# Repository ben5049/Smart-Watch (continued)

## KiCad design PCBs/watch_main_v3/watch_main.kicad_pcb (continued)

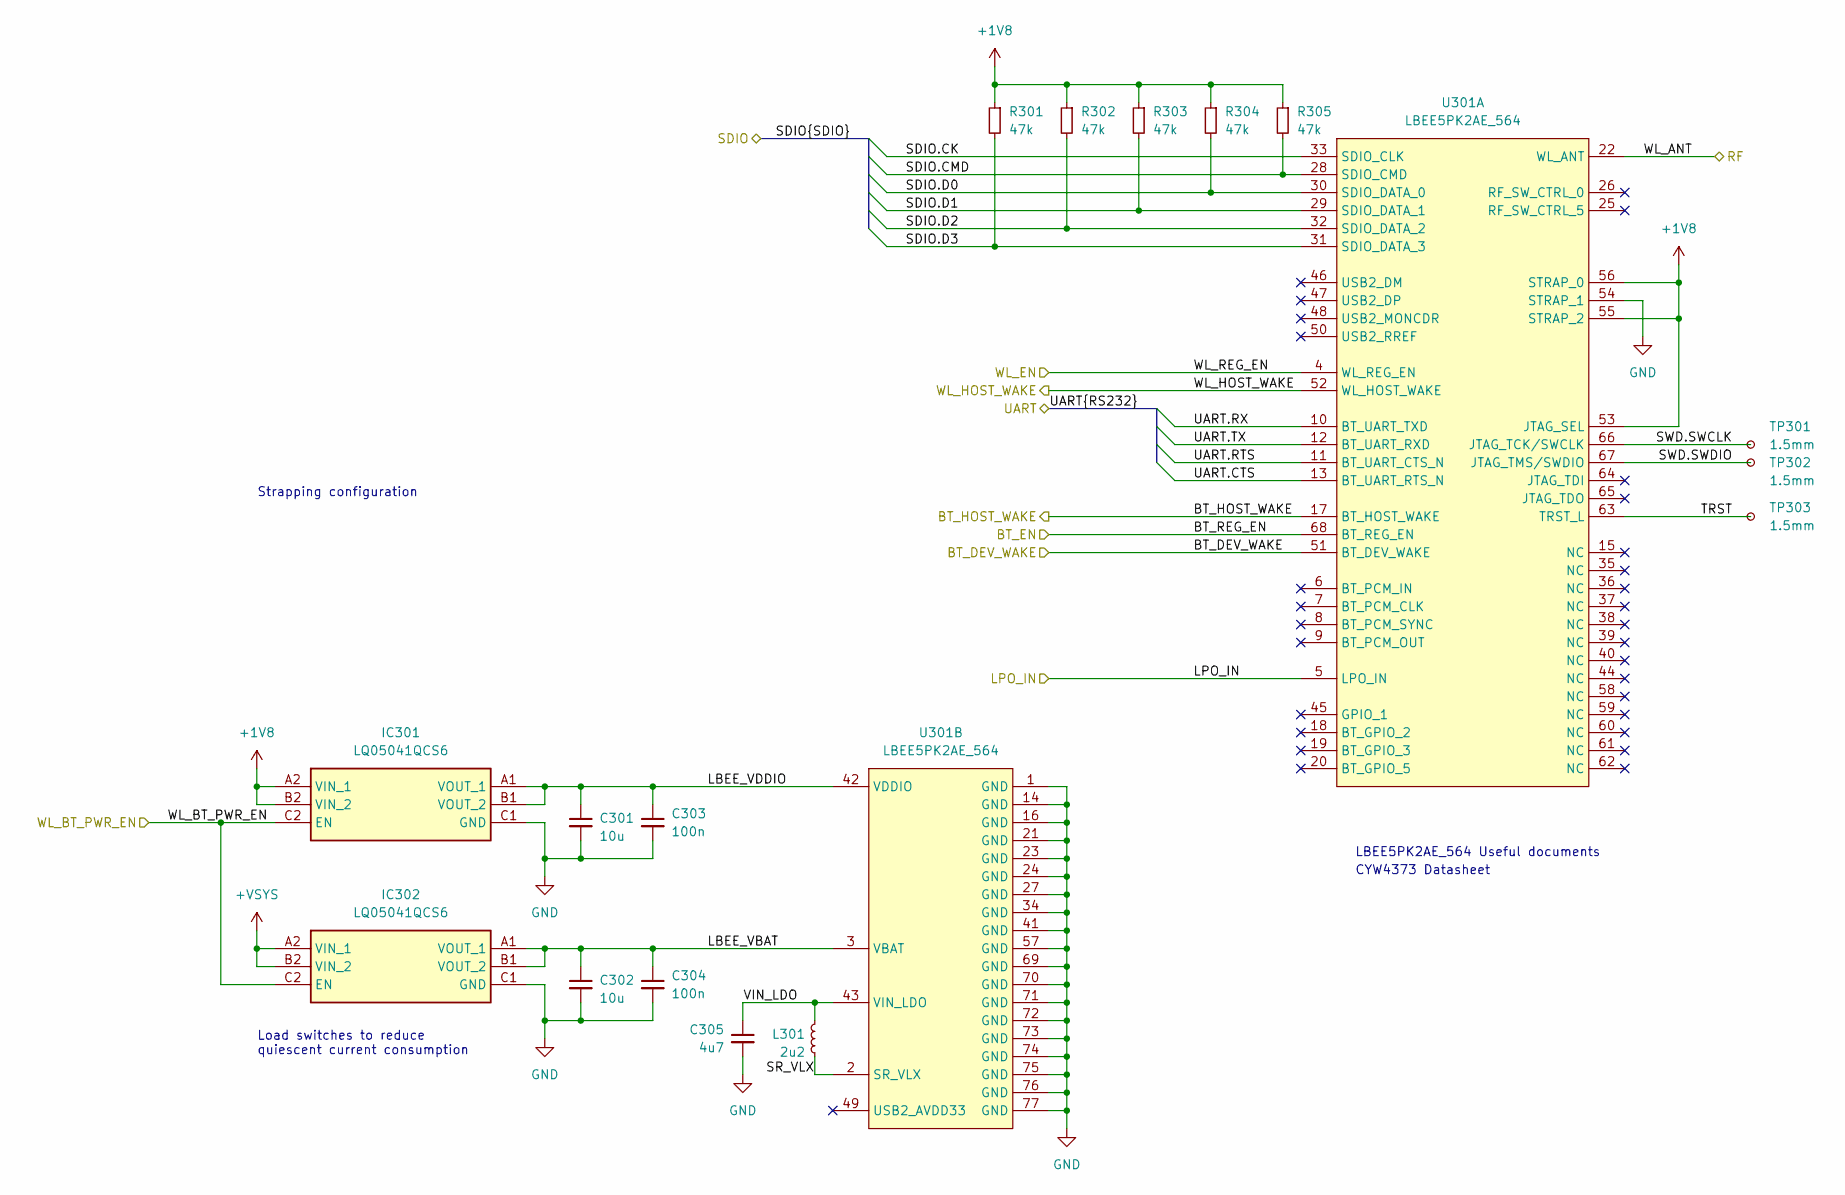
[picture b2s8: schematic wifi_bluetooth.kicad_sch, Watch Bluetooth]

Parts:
C301, C302: 10u; C_0402_1005Metric
C303, C304: 100n; C_0402_1005Metric
C305: 4u7; C_0402_1005Metric
IC301, IC302: LQ05041QCS6; BGA6C50P2X3_97X147X60; Manufacturer_Part_Number LQ05041QCS6
L301: 2u2; L_Murata_DFE201610P
R301, R302, R303, R304, R305: 47k; R_0402_1005Metric
TP301, TP302, TP303: 1.5mm; TestPoint_Pad_D1.5mm
U301: LBEE5PK2AE_564; LBEE5PK2AE-564

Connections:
+1V8: IC301.A2 (VIN_1), IC301.B2 (VIN_2), R301.1, R302.1, R303.1, R304.1, R305.1, U301.53 (JTAG_SEL), U301.55 (STRAP_2), U301.56 (STRAP_0); also elsewhere on the board
+VSYS: IC302.A2 (VIN_1), IC302.B2 (VIN_2); also elsewhere on the board
/BT_DEV_WAKE: U301.51 (BT_DEV_WAKE); also elsewhere on the board
/BT_EN: U301.68 (BT_REG_EN); also elsewhere on the board
/BT_HOST_WAKE: U301.17 (BT_HOST_WAKE); also elsewhere on the board
/RF_2.4G/5G: U301.22 (WL_ANT); also elsewhere on the board
/SDMMC2.CK: U301.33 (SDIO_CLK); also elsewhere on the board
/SDMMC2.CMD: R305.2, U301.28 (SDIO_CMD); also elsewhere on the board
/SDMMC2.D0: R304.2, U301.30 (SDIO_DATA_0); also elsewhere on the board
/SDMMC2.D1: R303.2, U301.29 (SDIO_DATA_1); also elsewhere on the board
/SDMMC2.D2: R302.2, U301.32 (SDIO_DATA_2); also elsewhere on the board
/SDMMC2.D3: R301.2, U301.31 (SDIO_DATA_3); also elsewhere on the board
/USART2.CTS: U301.13 (BT_UART_RTS_N); also elsewhere on the board
/USART2.RTS: U301.11 (BT_UART_CTS_N); also elsewhere on the board
/USART2.RX: U301.10 (BT_UART_TXD); also elsewhere on the board
/USART2.TX: U301.12 (BT_UART_RXD); also elsewhere on the board
/WL_BT_PWR_EN: IC301.C2 (EN), IC302.C2 (EN); also elsewhere on the board
/WL_EN: U301.4 (WL_REG_EN); also elsewhere on the board
/WL_HOST_WAKE: U301.52 (WL_HOST_WAKE); also elsewhere on the board
/WL_LPO_IN: U301.5 (LPO_IN); also elsewhere on the board
/WiFi and Bluetooth/LBEE_VBAT: C302.1, C304.1, IC302.A1 (VOUT_1), IC302.B1 (VOUT_2), U301.3 (VBAT)
/WiFi and Bluetooth/LBEE_VDDIO: C301.1, C303.1, IC301.A1 (VOUT_1), IC301.B1 (VOUT_2), U301.42 (VDDIO)
/WiFi and Bluetooth/SR_VLX: L301.2, U301.2 (SR_VLX)
/WiFi and Bluetooth/SWD.SWCLK: TP301.1, U301.66 (JTAG_TCK/SWCLK)
/WiFi and Bluetooth/SWD.SWDIO: TP302.1, U301.67 (JTAG_TMS/SWDIO)
/WiFi and Bluetooth/TRST: TP303.1, U301.63 (TRST_L)
/WiFi and Bluetooth/VIN_LDO: C305.1, L301.1, U301.43 (VIN_LDO)
GND: C301.2, C302.2, C303.2, C304.2, C305.2, IC301.C1 (GND), IC302.C1 (GND), U301.1 (GND), U301.14 (GND), U301.16 (GND), U301.21 (GND), U301.23 (GND), U301.24 (GND), U301.27 (GND), U301.34 (GND), U301.41 (GND), U301.54 (STRAP_1), U301.57 (GND), U301.69 (GND), U301.70 (GND), U301.71 (GND), U301.72 (GND), U301.73 (GND), U301.74 (GND), U301.75 (GND), U301.76 (GND), U301.77 (GND); also elsewhere on the board

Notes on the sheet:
Strapping configuration
LBEE5PK2AE_564 Useful documents
Load switches to reduce quiescent current consumption
CYW4373 Datasheet

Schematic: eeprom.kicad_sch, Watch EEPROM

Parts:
IC1801: M24256X-FCU6T_VF; BGA4C50P2X2_70X98X33; Mouser Part Number 511-M24256X-FCU6T/VF

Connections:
+1V8: IC1801.A1 (VCC); also elsewhere on the board
/I2C1.SCL: IC1801.A2 (SCL); also elsewhere on the board
/I2C1.SDA: IC1801.B1 (SDA); also elsewhere on the board
GND: IC1801.B2 (VSS); also elsewhere on the board

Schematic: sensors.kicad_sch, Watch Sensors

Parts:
C1301: 220n; C_0402_1005Metric
C1302, C1304, C1305, C1306, C1307: 100n; C_0402_1005Metric
C1303: 10u; C_0402_1005Metric
IC1301: IIS2MDCTR; Mouser Part Number 511-IIS2MDCTR
IC1302: OPT3004DNPR; SON65P200X200X65-7N-D; Mouser Part Number 595-OPT3004DNPR
U1301: LSM6DSO16IS; LGA14_LSM6_STM

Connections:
+1V8: C1302.1, C1303.1, C1304.1, C1305.1, C1306.1, C1307.1, IC1301.9 (VDD), IC1301.10 (VDD_IO), IC1302.1 (VDD), U1301.2 (MSDA), U1301.3 (MSCL), U1301.5 (VDD_IO), U1301.8 (VDD); also elsewhere on the board
/ALS_INT: IC1302.5 (INT); also elsewhere on the board
/I2C3.SCL: IC1301.1 (SCL/SPC), IC1302.4 (SCL); also elsewhere on the board
/I2C3.SDA: IC1301.4 (SDA/SDI/SDO), IC1302.6 (SDA); also elsewhere on the board
/IMU_INT1: U1301.4 (INT1); also elsewhere on the board
/IMU_INT2: U1301.9 (INT2); also elsewhere on the board
/MAG_INT: IC1301.7 (INT/DRDY); also elsewhere on the board
/SPI1.CS: U1301.12 (CS); also elsewhere on the board
/SPI1.MISO: U1301.1 (SDO/SA0); also elsewhere on the board
/SPI1.MOSI: U1301.14 (SDA); also elsewhere on the board
/SPI1.SCK: U1301.13 (SCL); also elsewhere on the board
/Sensors/C1: C1301.1, IC1301.5 (C1)
GND: C1301.2, C1302.2, C1303.2, C1304.2, C1305.2, C1306.2, C1307.2, IC1301.6 (GND_1), IC1301.8 (GND_2), IC1302.2 (ADDR), IC1302.3 (GND), IC1302.7 (EP), U1301.6 (GND), U1301.7 (GND); also elsewhere on the board

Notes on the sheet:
Address = 0x1E
Address = 0x6A (SA0=0)
Address = 0x44 (ADDR=0)
Typical application: LSM6DSO16IS datasheet p25
Typical application: IIS2MDCTR datasheet p19
Typical application: OPT3004 datasheet p19

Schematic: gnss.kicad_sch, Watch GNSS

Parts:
C401: 10n; C_0402_1005Metric
C402: 120p; C_0402_1005Metric
C403: 100n; C_0402_1005Metric
FL401: B39162B4327P810; mouser part number 871-B39162B4327P810; digikey description FILTER SAW 5SMD
IC401: BGA725L6E6327FTSA1; BGS12SN6E6327XTSA1; Mouser Part Number 726-BGA725L6E6327FTS
L401: 7n5; L_0402_1005Metric
R401: 10k; R_0402_1005Metric
U401: TESEO-LIV3FL; TESEOLIV3FL; Mouser Part Number 511-TESEO-LIV4FTR

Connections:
+1V8: C403.1, U401.6 (VBAT), U401.7 (VCCIO), U401.8 (VCC); also elsewhere on the board
/GNSS/ANT_OFF: IC401.6 (PON), R401.1, U401.13 (ANT_OFF)
/GNSS/LNA_IN: IC401.5 (AI), L401.2
/GNSS/LNA_OUT: FL401.1 (IN), IC401.3 (AO)
/GNSS/RF_IN: C402.2, U401.11 (RF_IN)
/GNSS/SAW_OUT: C402.1, FL401.4 (OUT)
/GNSS/VCC_RF: C401.1, IC401.2 (VCC), U401.14 (VCC_RF)
/GNSS_PPS: U401.4 (PPS); also elsewhere on the board
/GNSS_RST: U401.9 (NRESET); also elsewhere on the board
/GNSS_WAKEUP: U401.5 (WAKEUP); also elsewhere on the board
/RF_1.575G: L401.1; also elsewhere on the board
/USART1.RX: U401.2 (UART-TX); also elsewhere on the board
/USART1.TX: U401.3 (UART-RX); also elsewhere on the board
GND: C401.2, C403.2, FL401.2 (GND_1), FL401.3 (GND_2), FL401.5 (GND_3), IC401.1 (GND), IC401.4 (GNDRF), R401.2, U401.1 (GND), U401.10 (GND_RF_1), U401.12 (GND_RF_2); also elsewhere on the board

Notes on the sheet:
UM2980 p12

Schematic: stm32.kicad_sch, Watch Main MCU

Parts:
C801, C802, C803, C804: 6p; C_0402_1005Metric
R801, R802, R803, R804, R805, R806, R807, R808, R809, R810, R811, R812: 4k7; R_0402_1005Metric
TP801, TP802, TP803, TP804: 1.5mm; TestPoint_Pad_D1.5mm
U801: STM32U5G9ZJJ6Q; UFBGA144_STM
Y801: 16MHz; Crystal_SMD_2016-4Pin_2.0x1.6mm
Y802: 32.768kHz; Crystal_SMD_2012-2Pin_2.0x1.2mm

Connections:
+1V8: R801.1, R802.1, R803.1, R804.1, R805.1, R806.1, R807.1, R808.1, R810.1, R812.1; also elsewhere on the board
+3V3: R809.1, R811.1; also elsewhere on the board
/ADF1_CCK0: U801.K6 (PE9); also elsewhere on the board
/ADF1_SDI0: U801.J7 (PE10); also elsewhere on the board
/ALS_INT: U801.J6 (PG1); also elsewhere on the board
/AVDDEN: U801.D3 (PE6); also elsewhere on the board
/AVDD_ADC: U801.M2 (PA3); also elsewhere on the board
/BTN: U801.M9 (PB15); also elsewhere on the board
/BT_DEV_WAKE: U801.E11 (PI2); also elsewhere on the board
/BT_EN: U801.F11 (PI0); also elsewhere on the board
/BT_HOST_WAKE: U801.E12 (PI3); also elsewhere on the board
/DISPLAY_RST: U801.A3 (PH3_BOOT0); also elsewhere on the board
/DSI.CKN: U801.F1 (DSI_CKN); also elsewhere on the board
/DSI.CKP: U801.F2 (DSI_CKP); also elsewhere on the board
/DSI.D0N: U801.E1 (DSI_D0N); also elsewhere on the board
/DSI.D0P: U801.E2 (DSI_D0P); also elsewhere on the board
/DSI_TE: U801.C5 (PB7); also elsewhere on the board
/ELVDD_ADC: U801.L3 (PA4); also elsewhere on the board
/ELVSS_ADC: U801.L1 (PC3); also elsewhere on the board
/FLASH_INT: U801.G9 (PC6); also elsewhere on the board
/FLASH_RST: U801.H12 (PH13); also elsewhere on the board
/FLASH_RSTO: U801.F9 (PC7); also elsewhere on the board
/GNSS_PPS: U801.A7 (PG12); also elsewhere on the board
/GNSS_RST: U801.B6 (PG15); also elsewhere on the board
/GNSS_WAKEUP: U801.A6 (PG14); also elsewhere on the board
/GPIO1: U801.G5 (PC2); also elsewhere on the board
/GPIO2: U801.G4 (PF2); also elsewhere on the board
/HR_INT: U801.L11 (PD10); also elsewhere on the board
/I2C1.SCL: R802.2, U801.A4 (PB6); also elsewhere on the board
/I2C1.SDA: R804.2, U801.A2 (PB9); also elsewhere on the board
/I2C2.SCL: R806.2, U801.M10 (PB13); also elsewhere on the board
/I2C2.SDA: R808.2, U801.L7 (PB11); also elsewhere on the board
/I2C3.SCL: R810.2, U801.K2 (PC0); also elsewhere on the board
/I2C3.SDA: R812.2, U801.K1 (PC1); also elsewhere on the board
/I2C4.SCL: R801.2, U801.K11 (PD12); also elsewhere on the board
/I2C4.SDA: R803.2, U801.K9 (PD13); also elsewhere on the board
/I2C5.SCL: R805.2, U801.E7 (PD1); also elsewhere on the board
/I2C5.SDA: R807.2, U801.D8 (PD0); also elsewhere on the board
/I2C6.SCL: R809.2, U801.F4 (PF1); also elsewhere on the board
/I2C6.SDA: R811.2, U801.E5 (PF0); also elsewhere on the board
/IMU_INT1: U801.C4 (PE5); also elsewhere on the board
/IMU_INT2: U801.E4 (PC13); also elsewhere on the board
/LRA_EN: U801.L12 (PD14); also elsewhere on the board
/MAG_INT: U801.H8 (PE8); also elsewhere on the board
/OSPI1.CLKN: U801.B5; also elsewhere on the board
/OSPI1.CLKP: U801.K8 (PB10); also elsewhere on the board
/OSPI1.CS: U801.M5 (PE11); also elsewhere on the board
/OSPI1.DQS: U801.H6 (PB2); also elsewhere on the board
/OSPI1.IO0: U801.J8 (PE12); also elsewhere on the board
/OSPI1.IO1: U801.L6 (PE13); also elsewhere on the board
/OSPI1.IO2: U801.K7 (PE14); also elsewhere on the board
/OSPI1.IO3: U801.M6 (PE15); also elsewhere on the board
/OSPI1.IO4: U801.K12 (PH9); also elsewhere on the board
/OSPI1.IO5: U801.J12 (PH10); also elsewhere on the board
/OSPI1.IO6: U801.J11 (PH11); also elsewhere on the board
/OSPI1.IO7: U801.H11 (PH12); also elsewhere on the board
/PWR_ENCHG: U801.M11 (PD8); also elsewhere on the board
/PWR_INT: U801.K10 (PD9); also elsewhere on the board
/SDMMC1.CK: U801.A11 (PC12); also elsewhere on the board
/SDMMC1.CKIN: U801.B4 (PB8); also elsewhere on the board
/SDMMC1.CMD: U801.B9 (PD2); also elsewhere on the board
/SDMMC1.D0: U801.D12 (PC8); also elsewhere on the board
/SDMMC1.D1: U801.F8 (PC9); also elsewhere on the board
/SDMMC1.D2: U801.B10 (PC10); also elsewhere on the board
/SDMMC1.D3: U801.C8 (PC11); also elsewhere on the board
/SDMMC2.CK: U801.D7 (PD6); also elsewhere on the board
/SDMMC2.CMD: U801.A9 (PD7); also elsewhere on the board
/SDMMC2.D0: U801.L10 (PB14); also elsewhere on the board
/SDMMC2.D1: U801.D11 (PA8); also elsewhere on the board
/SDMMC2.D2: U801.D6 (PB3); also elsewhere on the board
/SDMMC2.D3: U801.A5 (PB4); also elsewhere on the board
/SD_CD: U801.K5 (PG0); also elsewhere on the board
/SD_EN: U801.L5 (PE7); also elsewhere on the board
/SPI1.CS: U801.J5 (PB0); also elsewhere on the board
/SPI1.MISO: U801.M3 (PA6); also elsewhere on the board
/SPI1.MOSI: U801.L4 (PA7); also elsewhere on the board
/SPI1.SCK: U801.K4 (PA5); also elsewhere on the board
/STM32/GPIO3: TP804.1, U801.C6 (PG13)
/STM32/OSC32_IN: C803.2, U801.C1 (PC14-OSC32_IN), Y802.2
/STM32/OSC32_OUT: C804.2, U801.D2 (PC15-OSC32_OUT), Y802.1
/STM32/OSC_IN: C801.2, U801.H2 (PH0-OSC_IN), Y801.3
/STM32/OSC_OUT: C802.2, U801.J1 (PH1-OSC_OUT), Y801.1
/STM32/SWD.RST: TP803.1, U801.J2 (NRST)
/STM32/SWD.SWCLK: TP802.1, U801.B11 (PA14)
/STM32/SWD.SWDIO: TP801.1, U801.C10 (PA13)
/SWIRE_IN: U801.B3 (PE0); also elsewhere on the board
/SWIRE_OUT: U801.C3 (PE4); also elsewhere on the board
/TOUCH_INT: U801.L9 (PD11); also elsewhere on the board
/TOUCH_RST: U801.H9 (PD15); also elsewhere on the board
/TP_INT: U801.B1 (PE2); also elsewhere on the board
/TP_RST: U801.B2 (PE3); also elsewhere on the board
/UART4.RX: U801.K3 (PA1); also elsewhere on the board
/UART4.TX: U801.H4 (PA0); also elsewhere on the board
/USART1.RX: U801.A8 (PG10); also elsewhere on the board
/USART1.TX: U801.B7 (PG9); also elsewhere on the board
/USART2.CTS: U801.A10 (PD3); also elsewhere on the board
/USART2.RTS: U801.C7 (PD4); also elsewhere on the board
/USART2.RX: U801.C9 (PA15); also elsewhere on the board
/USART2.TX: U801.B8 (PD5); also elsewhere on the board
/USB.DN: U801.C12 (PA11); also elsewhere on the board
/USB.DP: U801.C11 (PA12); also elsewhere on the board
/VBUS_ADC: U801.M4 (PB1); also elsewhere on the board
/WL_BT_PWR_EN: U801.G12 (PH15); also elsewhere on the board
/WL_EN: U801.F12 (PI1); also elsewhere on the board
/WL_HOST_WAKE: U801.G11 (PH14); also elsewhere on the board
/WL_LPO_IN: U801.L2 (PA2); also elsewhere on the board
GND: C801.1, C802.1, C803.1, C804.1, Y801.2, Y801.4; also elsewhere on the board

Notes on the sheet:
CL = 8pF CS = 5pF ∴ CLx = 6pF
CL = 7pF CS = 4pF ∴ CLx = 6pF

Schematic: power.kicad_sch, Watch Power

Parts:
C201: 2u2; C_0402_1005Metric
C202: 1u; C_0402_1005Metric
C203, C204, C205, C206, C207, C208: 10u; C_0402_1005Metric
IC201: ADP5360ACBZ-2-R7; ADP5360ACBZ1R7; Mouser Part Number 584-ADP5360ACBZ-2-R7
L201, L202: 4u7; L_Murata_DFE201610P
Q201: DMP2104LP-7; DMP2104LP7; Mouser Part Number 621-DMP2104LP-7
R201: 10k; R_0402_1005Metric
R202: 100k; R_0402_1005Metric
TP201, TP202, TP203, TP204: 1.5mm; TestPoint_Pad_D1.5mm

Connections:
+1V8: C206.1, IC201.D1 (FB1), L201.2; also elsewhere on the board
+3V3: C207.1, IC201.A3 (VOUT2); also elsewhere on the board
+VBAT: C203.1, IC201.C6 (BSNS), IC201.D6 (ISOB), TP201.1; also elsewhere on the board
+VSYS: C204.1, C205.1, C208.1, IC201.C1 (VIN2), IC201.D2 (VID1), IC201.E2 (EN1), IC201.E6 (VSYS), IC201.F2 (VIN1); also elsewhere on the board
/BTN: IC201.E4 (~MR), R201.2; also elsewhere on the board
/I2C2.SCL: IC201.A4 (SCL); also elsewhere on the board
/I2C2.SDA: IC201.A5 (SDA); also elsewhere on the board
/PWR_ENCHG: IC201.F3 (ENCHG); also elsewhere on the board
/PWR_INT: IC201.A6 (~INT); also elsewhere on the board
/Power/SWA_3V3: IC201.B1 (SW2A), L202.1
/Power/SWB_3V3: IC201.A2 (SW2B), L202.2
/Power/SW_1V8: IC201.E1 (SW1), L201.1
/Power/THR: IC201.B6 (THR), R202.1
/Power/VBUS_PROTECTED: C201.1, IC201.F6 (VBUS), Q201.3 (S)
GND: C201.2, C202.2, C203.2, C204.2, C205.2, C206.2, C207.2, C208.2, IC201.A1 (PGND2), IC201.B2 (AGND2), IC201.B3 (ENSD), IC201.B4 (EN2), IC201.F1 (PGND1), IC201.F4 (AGND1), Q201.1 (G), R202.2, TP202.1, TP203.1, TP204.1; also elsewhere on the board
VBUS: Q201.2 (D); also elsewhere on the board
VDD: C202.1, IC201.F5 (VDD), R201.1

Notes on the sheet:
VID1 = VIN1 ∴ VOUT1 = 1V8 (ADP5360ACBZ-2-R7 p59)
INT needs to be pulled up by host
I2C Address: 0x46
I2C Pullups on STM32 sheet

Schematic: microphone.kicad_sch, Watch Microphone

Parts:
C1201: 100n; C_0402_1005Metric
MIC1201: IM70D122V01XTMA1; PG-TLGA-5-2_INF

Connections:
+1V8: C1201.1, MIC1201.1 (VDD); also elsewhere on the board
/ADF1_CCK0: MIC1201.2 (CLOCK); also elsewhere on the board
/ADF1_SDI0: MIC1201.3 (DATA); also elsewhere on the board
GND: C1201.2, MIC1201.4 (LR_SELECT), MIC1201.5 (GND); also elsewhere on the board

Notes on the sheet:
PDM Interface

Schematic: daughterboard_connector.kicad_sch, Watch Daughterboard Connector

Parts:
J701: AXG120144; Manufacturer_Part_Number AXG120144; Mouser Part Number 769-AXG120144
R701: 330k; R_0402_1005Metric
R702: 100k; R_0402_1005Metric

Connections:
+1V8: J701.2, J701.19; also elsewhere on the board
+3V3: J701.1, J701.20; also elsewhere on the board
+VBAT: J701.6, J701.15; also elsewhere on the board
/HR_INT: J701.12; also elsewhere on the board
/I2C4.SCL: J701.9; also elsewhere on the board
/I2C4.SDA: J701.11; also elsewhere on the board
/LRA_EN: J701.10; also elsewhere on the board
/VBUS_ADC: R701.2, R702.1; also elsewhere on the board
GND: J701.3, J701.4, J701.7, J701.8, J701.13, J701.14, J701.17, J701.18, R702.2; also elsewhere on the board
VBUS: J701.5, J701.16, R701.1; also elsewhere on the board

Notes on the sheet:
HR sensors address = 0x57
LRA driver address = 0x5A

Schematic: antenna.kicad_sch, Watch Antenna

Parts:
ANT1601: ANT161575TT-3000A1; ANT161575TT3000A1; Mouser Part Number 810-ANT161575TT-30A1
C1601: 43p; C_0402_1005Metric
C1602: 7p5; C_0402_1005Metric
L1601, L1604: 1n5; L_0402_1005Metric
L1602: 0n6; L_0402_1005Metric
L1603: 2n7; L_0402_1005Metric
R1601: 0R; R_0402_1005Metric
U1601: GPS_&_BT_Antenna_Keepout; GPS & BT Antenna

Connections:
/Antenna/Common: ANT1601.2 (COMMON_RADIATOR_ELECTRODE), R1601.1
/Antenna/Ft_2.4GHz: ANT1601.4 (FEED_POINT_FOR_2.4GHZ/5.5GHZ), C1602.1
/Antenna/Ft_5.5GHz: C1602.2, L1602.1
/Antenna/Ft_GPS: ANT1601.1 (FEED_POINT_FOR_GPS), C1601.2
/RF_1.575G: C1601.1, L1601.1; also elsewhere on the board
/RF_2.4G/5G: L1604.2; also elsewhere on the board
GND: L1601.2, L1603.2, R1601.2; also elsewhere on the board
unnamed: L1602.2, L1603.1, L1604.1

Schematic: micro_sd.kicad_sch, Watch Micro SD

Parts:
C1101: 10u; C_0402_1005Metric
C1102: 100n; C_0402_1005Metric
IC1101: LQ05041QCS6; BGA6C50P2X3_97X147X60; Manufacturer_Part_Number LQ05041QCS6
IC1102: NVT4858HKZ; Mouser Part Number 771-NVT4858HKZ
J1101: 105162-0001; Mouser Part Number 538-105162-0001

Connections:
+1V8: C1102.1, IC1102.15 (VCCA); also elsewhere on the board
+3V3: IC1101.A2 (VIN_1), IC1101.B2 (VIN_2), IC1102.14 (VCCB); also elsewhere on the board
/Micro SD/+3V3_SD: C1101.1, IC1101.A1 (VOUT_1), IC1101.B1 (VOUT_2), J1101.4 (VDD)
/Micro SD/CLK: IC1102.8 (CLKB), J1101.5 (CLK)
/Micro SD/CMD: IC1102.13 (CMDB), J1101.3 (CMD)
/Micro SD/DAT0: IC1102.10 (DAT0B), J1101.7 (DAT0)
/Micro SD/DAT1: IC1102.9 (DAT1B), J1101.8 (DAT1)
/Micro SD/DAT2: IC1102.12 (DAT2B), J1101.1 (DAT2)
/Micro SD/DAT3: IC1102.11 (DAT3B), J1101.2 (CD/DAT3)
/SDMMC1.CK: IC1102.5 (CLKA); also elsewhere on the board
/SDMMC1.CKIN: IC1102.6 (CLK_FB); also elsewhere on the board
/SDMMC1.CMD: IC1102.16 (CMDA); also elsewhere on the board
/SDMMC1.D0: IC1102.3 (DAT0A); also elsewhere on the board
/SDMMC1.D1: IC1102.4 (DAT1A); also elsewhere on the board
/SDMMC1.D2: IC1102.1 (DAT2A); also elsewhere on the board
/SDMMC1.D3: IC1102.2 (DAT3A); also elsewhere on the board
/SD_CD: J1101.9 (DET); also elsewhere on the board
/SD_EN: IC1101.C2 (EN); also elsewhere on the board
GND: C1101.2, C1102.2, IC1101.C1 (GND), IC1102.7 (GND), J1101.6 (VSS), J1101.10 (GND_1), J1101.11 (GND_2), J1101.12 (GND_3), J1101.13 (GND_4), J1101.14 (MP1), J1101.15 (MP2); also elsewhere on the board

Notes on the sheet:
CD needs to be pulled up by host
Active high EN

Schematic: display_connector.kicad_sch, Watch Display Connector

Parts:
J501: AXG130144; Mouser Part Number 667-AXG130144

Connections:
+1V8: J501.1, J501.2, J501.5; also elsewhere on the board
/AVDD: J501.3, J501.4; also elsewhere on the board
/DISPLAY_RST: J501.10; also elsewhere on the board
/DSI.CKN: J501.28; also elsewhere on the board
/DSI.CKP: J501.27; also elsewhere on the board
/DSI.D0N: J501.25; also elsewhere on the board
/DSI.D0P: J501.24; also elsewhere on the board
/DSI_TE: J501.11; also elsewhere on the board
/ELVDD: J501.16, J501.17, J501.18; also elsewhere on the board
/ELVSS: J501.13, J501.14, J501.15; also elsewhere on the board
/I2C5.SCL: J501.20; also elsewhere on the board
/I2C5.SDA: J501.21; also elsewhere on the board
/SWIRE_IN: J501.12; also elsewhere on the board
/TP_INT: J501.22; also elsewhere on the board
/TP_RST: J501.19; also elsewhere on the board
GND: J501.6, J501.7, J501.8, J501.9, J501.23, J501.26, J501.29; also elsewhere on the board

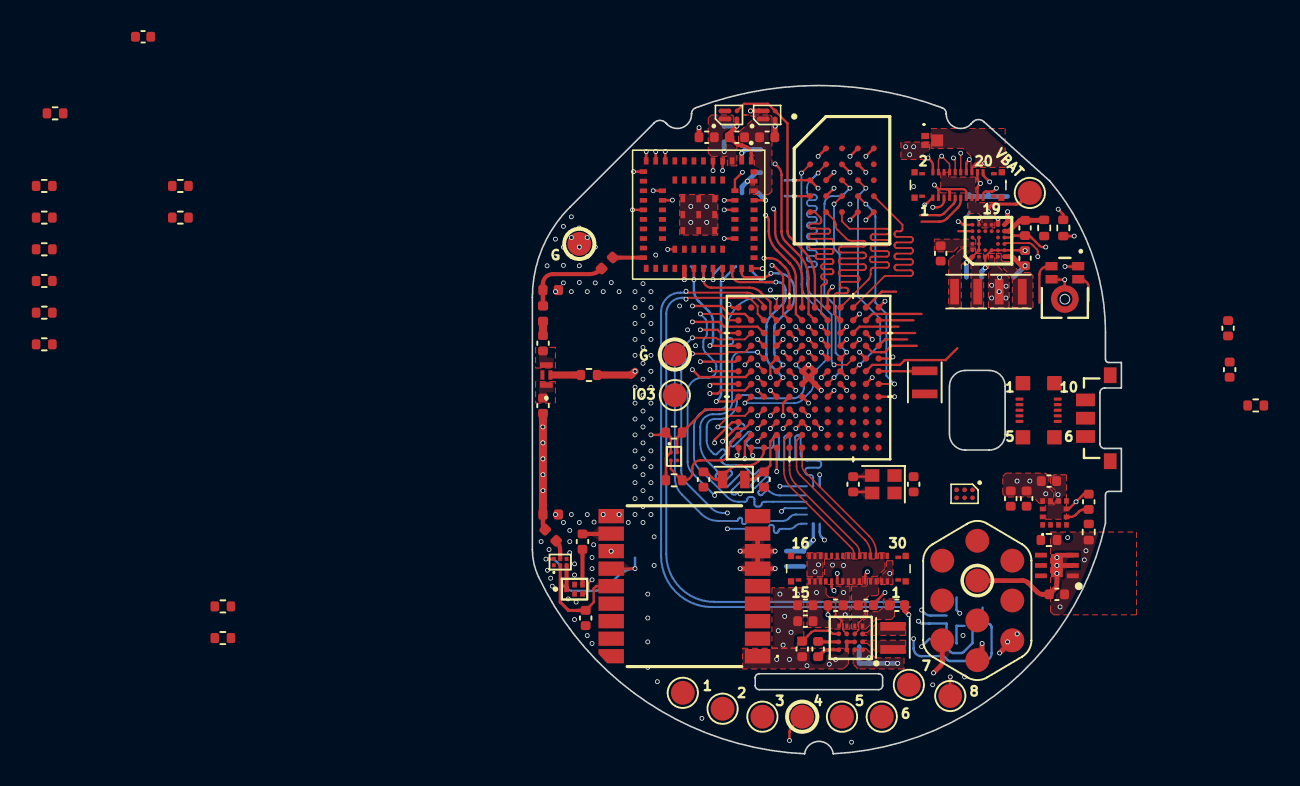
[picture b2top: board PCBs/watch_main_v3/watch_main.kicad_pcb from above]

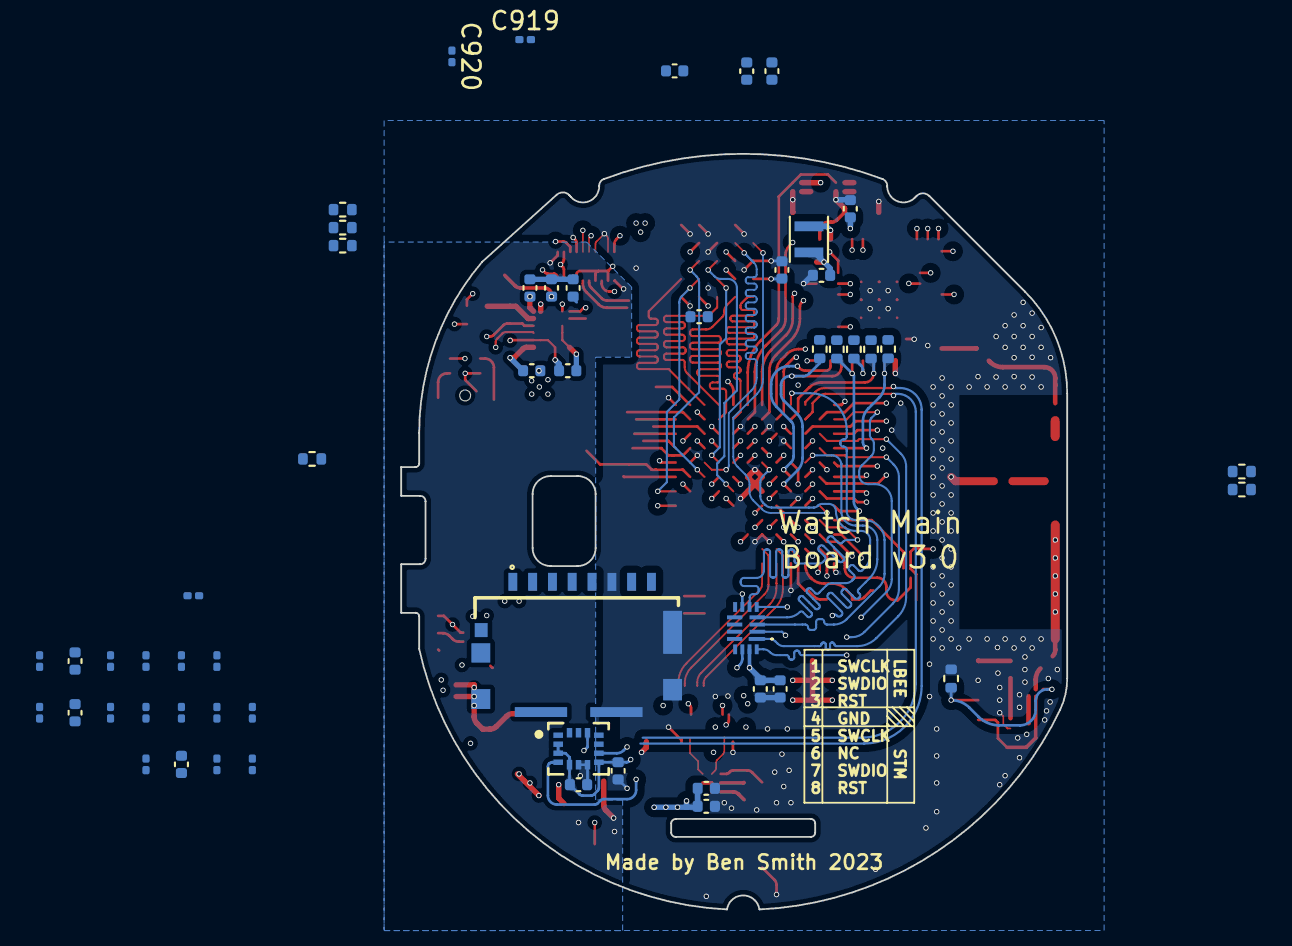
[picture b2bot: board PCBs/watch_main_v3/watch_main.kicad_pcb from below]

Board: 8 copper layers, 37.0 x 42.0 mm, 149 parts (54 on the bottom side), 156 nets.

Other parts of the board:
TP899: 1.5mm; TestPoint_Pad_D1.5mm

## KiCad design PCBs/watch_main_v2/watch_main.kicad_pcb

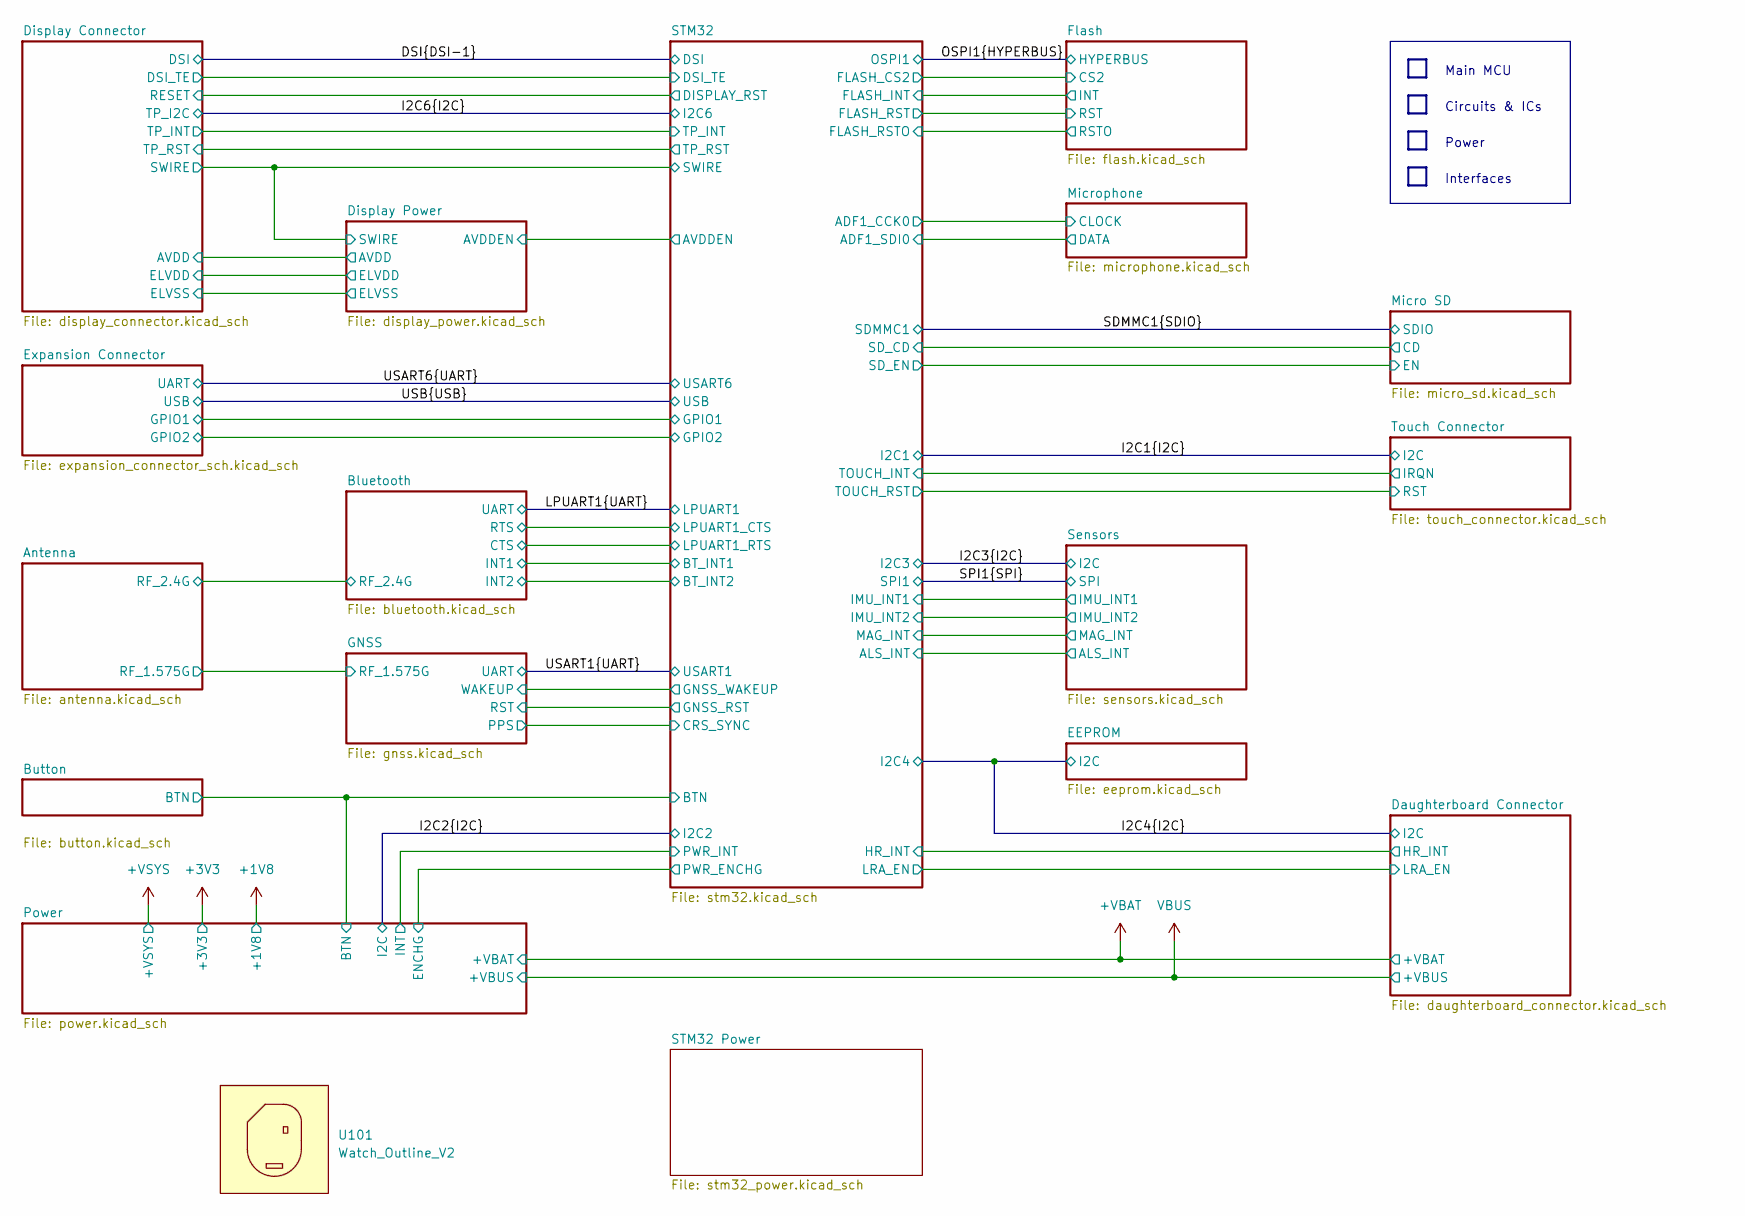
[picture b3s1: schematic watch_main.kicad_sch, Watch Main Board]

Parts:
U101: Watch_Outline_V2; Watch Outline V2

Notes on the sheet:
Interfaces
Circuits & ICs
Power
Main MCU

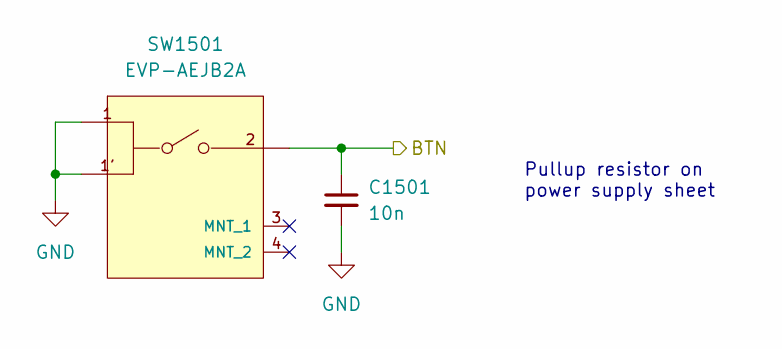
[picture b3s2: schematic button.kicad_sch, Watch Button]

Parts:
C1501: 10n; C_0402_1005Metric
SW1501: EVP-AEJB2A; Panasonic-EVP-AEJB2A-MFG; voltage rating DC 15V; mouser part number 667-EVP-AEJB2A; digikey description SWITCH TACTILE SPST-NO 0.02A 15V

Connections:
/STM32/BTN: C1501.1, SW1501.2; also elsewhere on the board
GND: C1501.2, SW1501.1, SW1501.1'; also elsewhere on the board

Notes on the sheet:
Pullup resistor on power supply sheet

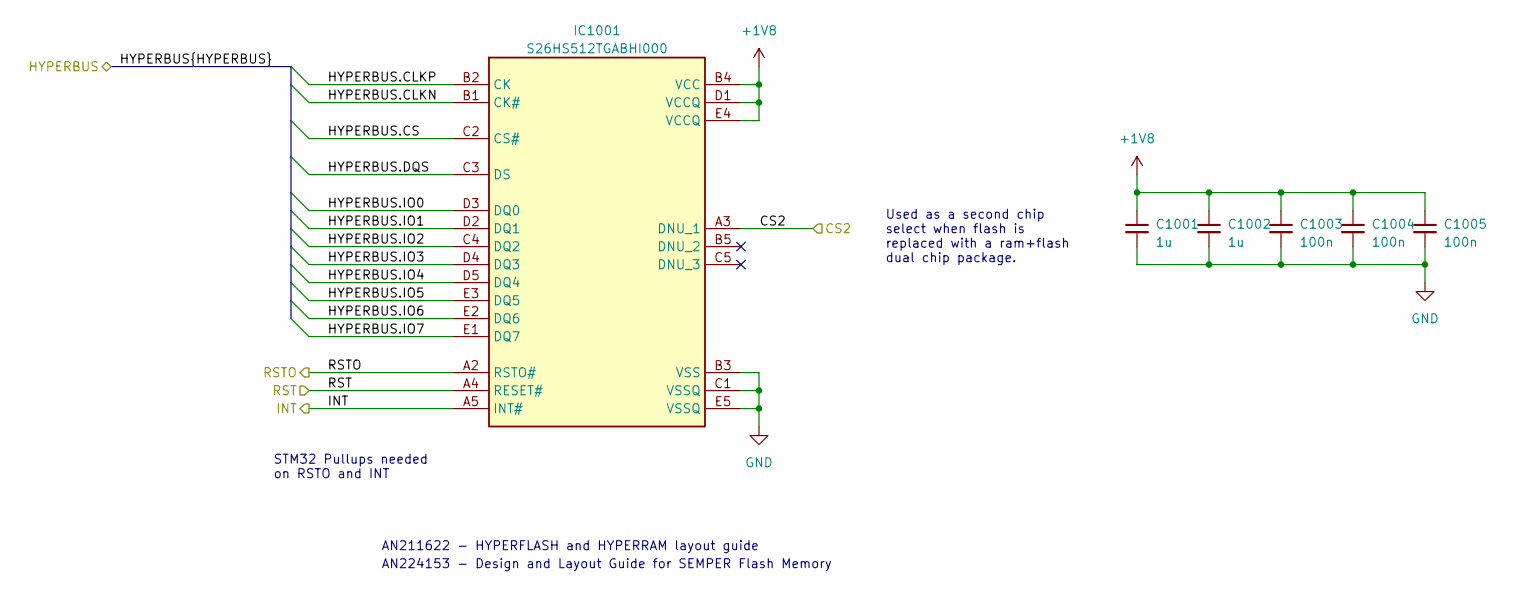
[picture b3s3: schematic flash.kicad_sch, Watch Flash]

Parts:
C1001, C1002: 1u; C_0402_1005Metric
C1003, C1004, C1005: 100n; C_0402_1005Metric
IC1001: S26HS512TGABHI000; BGA24C100P5X5_600X800X100; Mouser Part Number 727-S26HS512TGABHI00

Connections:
+1V8: C1001.1, C1002.1, C1003.1, C1004.1, C1005.1, IC1001.B4 (VCC), IC1001.D1 (VCCQ), IC1001.E4 (VCCQ); also elsewhere on the board
/Flash/CS2: IC1001.A3 (DNU_1); also elsewhere on the board
/Flash/INT: IC1001.A5 (INT#); also elsewhere on the board
/Flash/RST: IC1001.A4 (RESET#); also elsewhere on the board
/Flash/RSTO: IC1001.A2 (RSTO#); also elsewhere on the board
/OSPI1.CLKN: IC1001.B1 (CK#); also elsewhere on the board
/OSPI1.CLKP: IC1001.B2 (CK); also elsewhere on the board
/OSPI1.CS: IC1001.C2 (CS#); also elsewhere on the board
/OSPI1.DQS: IC1001.C3 (DS); also elsewhere on the board
/OSPI1.IO0: IC1001.D3 (DQ0); also elsewhere on the board
/OSPI1.IO1: IC1001.D2 (DQ1); also elsewhere on the board
/OSPI1.IO2: IC1001.C4 (DQ2); also elsewhere on the board
/OSPI1.IO3: IC1001.D4 (DQ3); also elsewhere on the board
/OSPI1.IO4: IC1001.D5 (DQ4); also elsewhere on the board
/OSPI1.IO5: IC1001.E3 (DQ5); also elsewhere on the board
/OSPI1.IO6: IC1001.E2 (DQ6); also elsewhere on the board
/OSPI1.IO7: IC1001.E1 (DQ7); also elsewhere on the board
GND: C1001.2, C1002.2, C1003.2, C1004.2, C1005.2, IC1001.B3 (VSS), IC1001.C1 (VSSQ), IC1001.E5 (VSSQ); also elsewhere on the board

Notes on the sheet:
STM32 Pullups needed on RSTO and INT
AN224153 - Design and Layout Guide for SEMPER Flash Memory
Used as a second chip select when flash is replaced with a ram+flash dual chip package.
AN211622 - HYPERFLASH and HYPERRAM layout guide

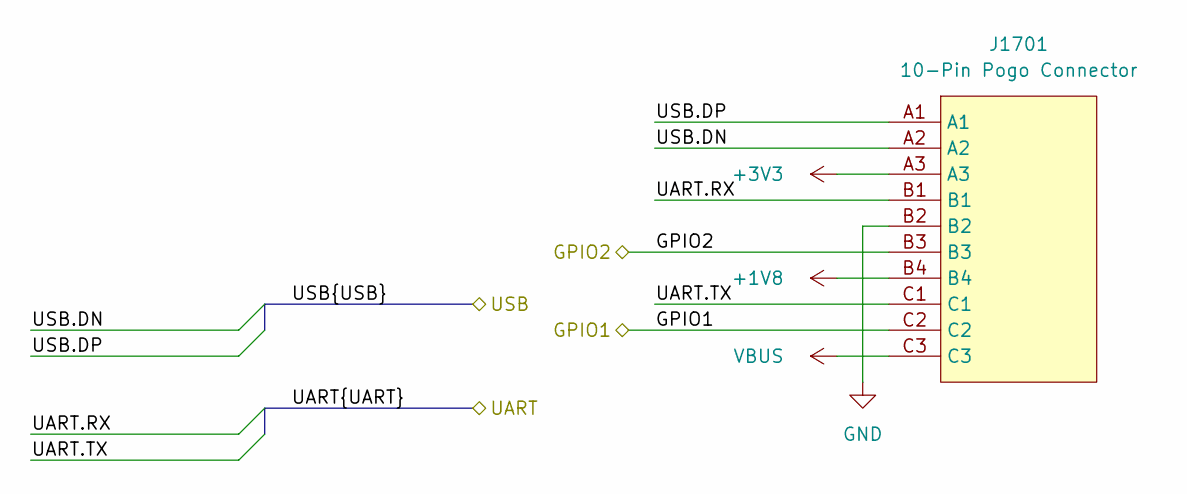
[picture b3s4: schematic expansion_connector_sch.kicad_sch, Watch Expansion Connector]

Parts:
J1701: 10-Pin Pogo Connector

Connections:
+1V8: J1701.B4; also elsewhere on the board
+3V3: J1701.A3; also elsewhere on the board
/Expansion Connector/GPIO1: J1701.C2; also elsewhere on the board
/Expansion Connector/GPIO2: J1701.B3; also elsewhere on the board
/USART6.RX: J1701.B1; also elsewhere on the board
/USART6.TX: J1701.C1; also elsewhere on the board
/USB.DN: J1701.A2; also elsewhere on the board
/USB.DP: J1701.A1; also elsewhere on the board
GND: J1701.B2; also elsewhere on the board
VBUS: J1701.C3; also elsewhere on the board
